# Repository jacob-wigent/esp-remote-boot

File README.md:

# esp-remote-boot
ESP8266 remote start device for desktop computers

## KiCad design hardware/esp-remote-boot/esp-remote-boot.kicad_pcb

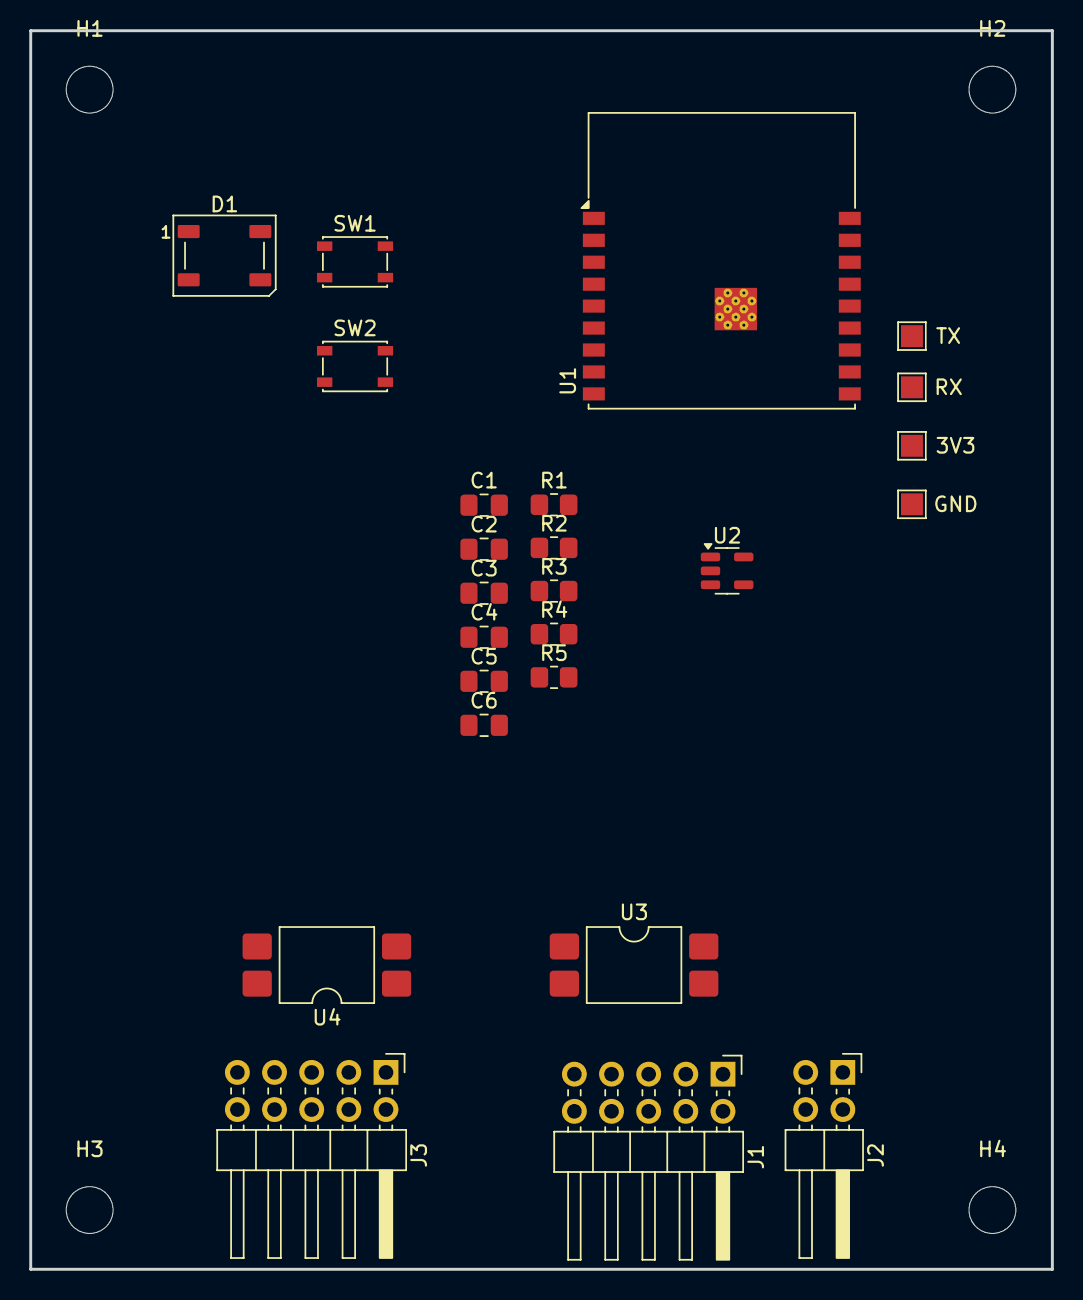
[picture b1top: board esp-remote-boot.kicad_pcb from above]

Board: 2 copper layers, 69.8 x 84.7 mm, 29 parts (0 on the bottom side), 18 nets, no tracks yet.

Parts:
3V3: 3V3; TestPoint_Pad_1.5x1.5mm
C1, C6: 1uF; C_0805_2012Metric_Pad1.18x1.45mm_HandSolder
C2: 10uF; C_0805_2012Metric_Pad1.18x1.45mm_HandSolder
C3, C4, C5: 0.1uF; C_0805_2012Metric_Pad1.18x1.45mm_HandSolder
D1: WS2812B; LED_WS2812B_PLCC4_5.0x5.0mm_P3.2mm
GND: 3V3; TestPoint_Pad_1.5x1.5mm
H1, H2, H3, H4: MountingHole; MountingHole_3.2mm_M3
J1: Header IN; PinHeader_2x05_P2.54mm_Horizontal
J2: USB Connector; PinHeader_2x02_P2.54mm_Horizontal
J3: Header OUT; PinHeader_2x05_P2.54mm_Horizontal
R1, R2, R3: 10k; R_0805_2012Metric_Pad1.20x1.40mm_HandSolder
R4: 220; R_0805_2012Metric_Pad1.20x1.40mm_HandSolder
R5: 390; R_0805_2012Metric_Pad1.20x1.40mm_HandSolder
RX: RX; TestPoint_Pad_1.5x1.5mm
SW1, SW2: Reset; SW_SPST_PTS810
TX: TX; TestPoint_Pad_1.5x1.5mm
U1: ESP32-C3-WROOM-02
U2: TLV75709PDBV; SOT-23-5
U3, U4: APC-817; SMDIP-4_W9.53mm

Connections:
5V_LED: J1.2, J3.2, R5.1
+3V3: 3V3.1, C2.1, C3.1, C6.1, D1.1 (VDD), R1.2, R2.2, R3.2, U1.1 (3V3), U2.5 (OUT)
+5V: C1.1, J2.2, U2.1 (IN), U2.3 (EN)
BTN_HIGH: J1.6, J3.6, U3.4
BTN_LOW: J1.8, J3.8, U3.3
EN: C4.1, R1.1, SW1.1, U1.2 (EN)
GND: C1.2, C2.2, C3.2, C4.2, C5.2, C6.2, D1.3 (VSS), GND.1, J2.1, SW1.2, SW2.2, U1.9 (GND), U1.19 (GND), U2.2 (GND), U3.2, U4.3
LED_GND: J1.4, J3.4, U4.2
unnamed: R4.2, U3.1
unnamed: R5.2, U4.1
unnamed: RX.1, U1.11 (IO20/RXD)
unnamed: TX.1, U1.12 (IO21/TXD)
PC_TRIGGER: R4.1, U1.6 (IO7)
STATUS_LED: D1.4 (DIN), U1.4 (IO5)
USB_D+: J2.4, U1.14 (IO19)
USB_D-: J2.3, U1.13 (IO18)
~BOOT: C5.1, R2.1, SW2.1, U1.8 (IO9)
~PC_STATUS: R3.1, U1.5 (IO6), U4.4

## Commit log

2025-07-31 Basic Wifi setup and Homekit
    Simple wifi setup portal and connection with jank homekit operation
2025-08-01 Switched to Lock
    Mostly working using lock accesory.
2025-08-02 LED and Button IO
2025-08-11 Pin changes for soldered board
2025-11-04 Modified WiFi Config
2025-11-04 Test
2025-12-16 KiCad Gitignore
2025-12-16 Schematic Connectors and Optocouplers
2026-03-09 Minor USB C Changes
